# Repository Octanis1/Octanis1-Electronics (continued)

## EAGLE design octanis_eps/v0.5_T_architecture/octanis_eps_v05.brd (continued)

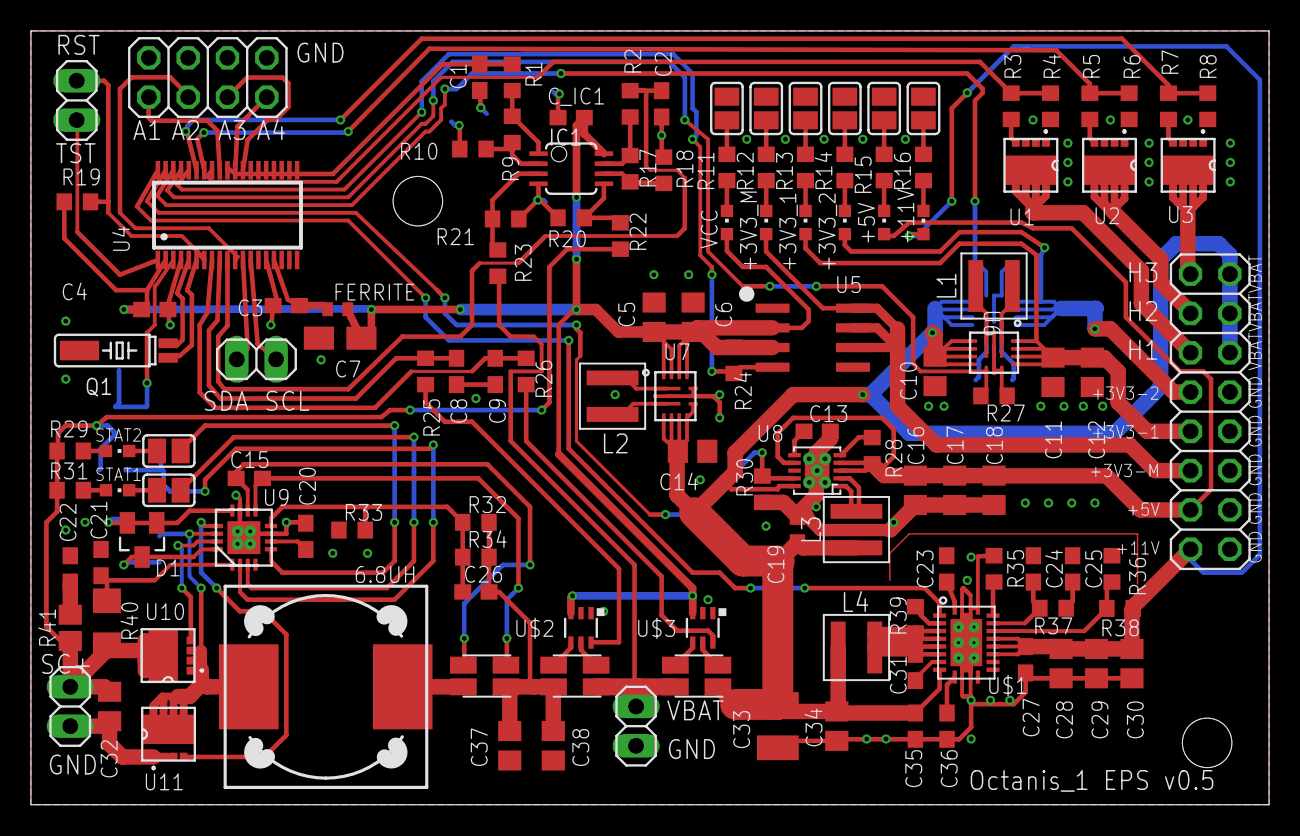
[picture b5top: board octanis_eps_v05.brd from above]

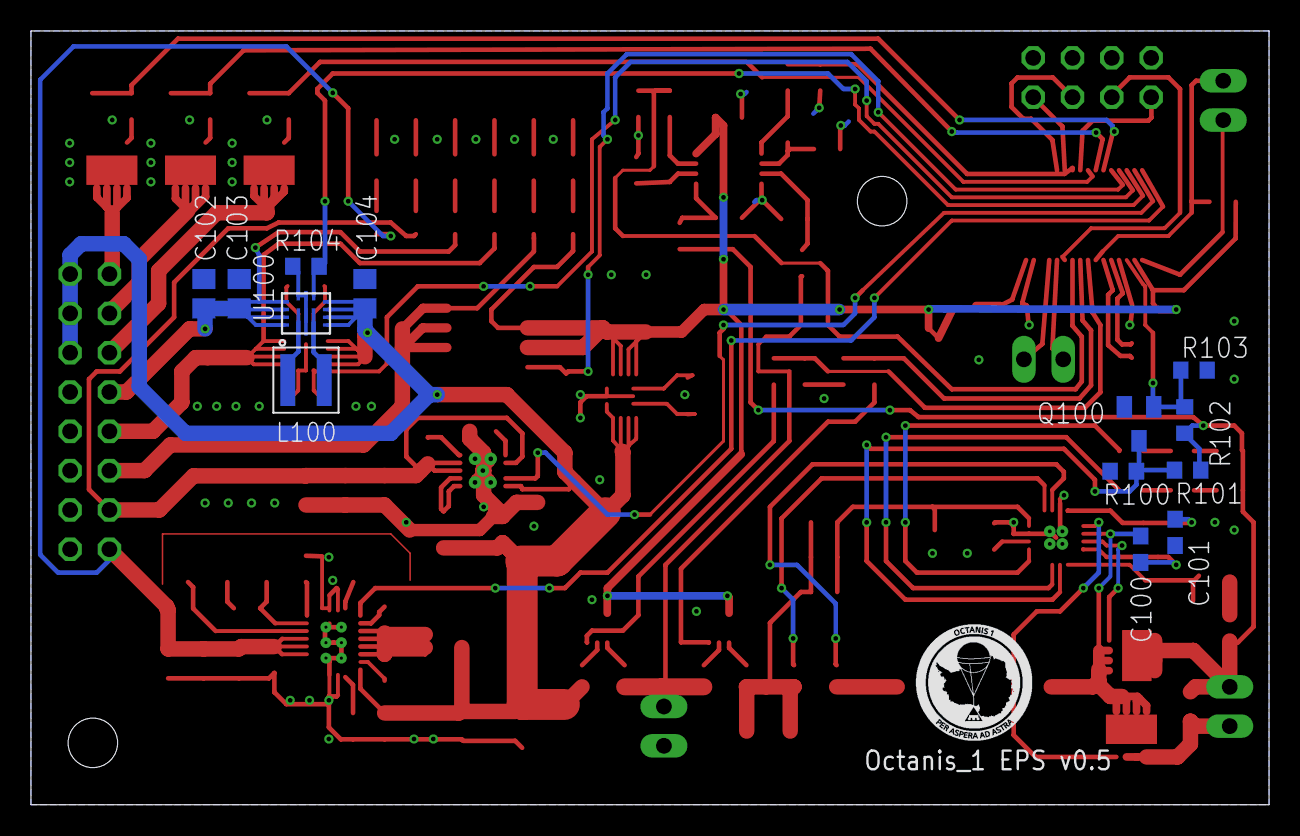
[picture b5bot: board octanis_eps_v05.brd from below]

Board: 2 copper layers, 80.0 x 50.0 mm, 141 parts (13 on the bottom side), 102 nets.

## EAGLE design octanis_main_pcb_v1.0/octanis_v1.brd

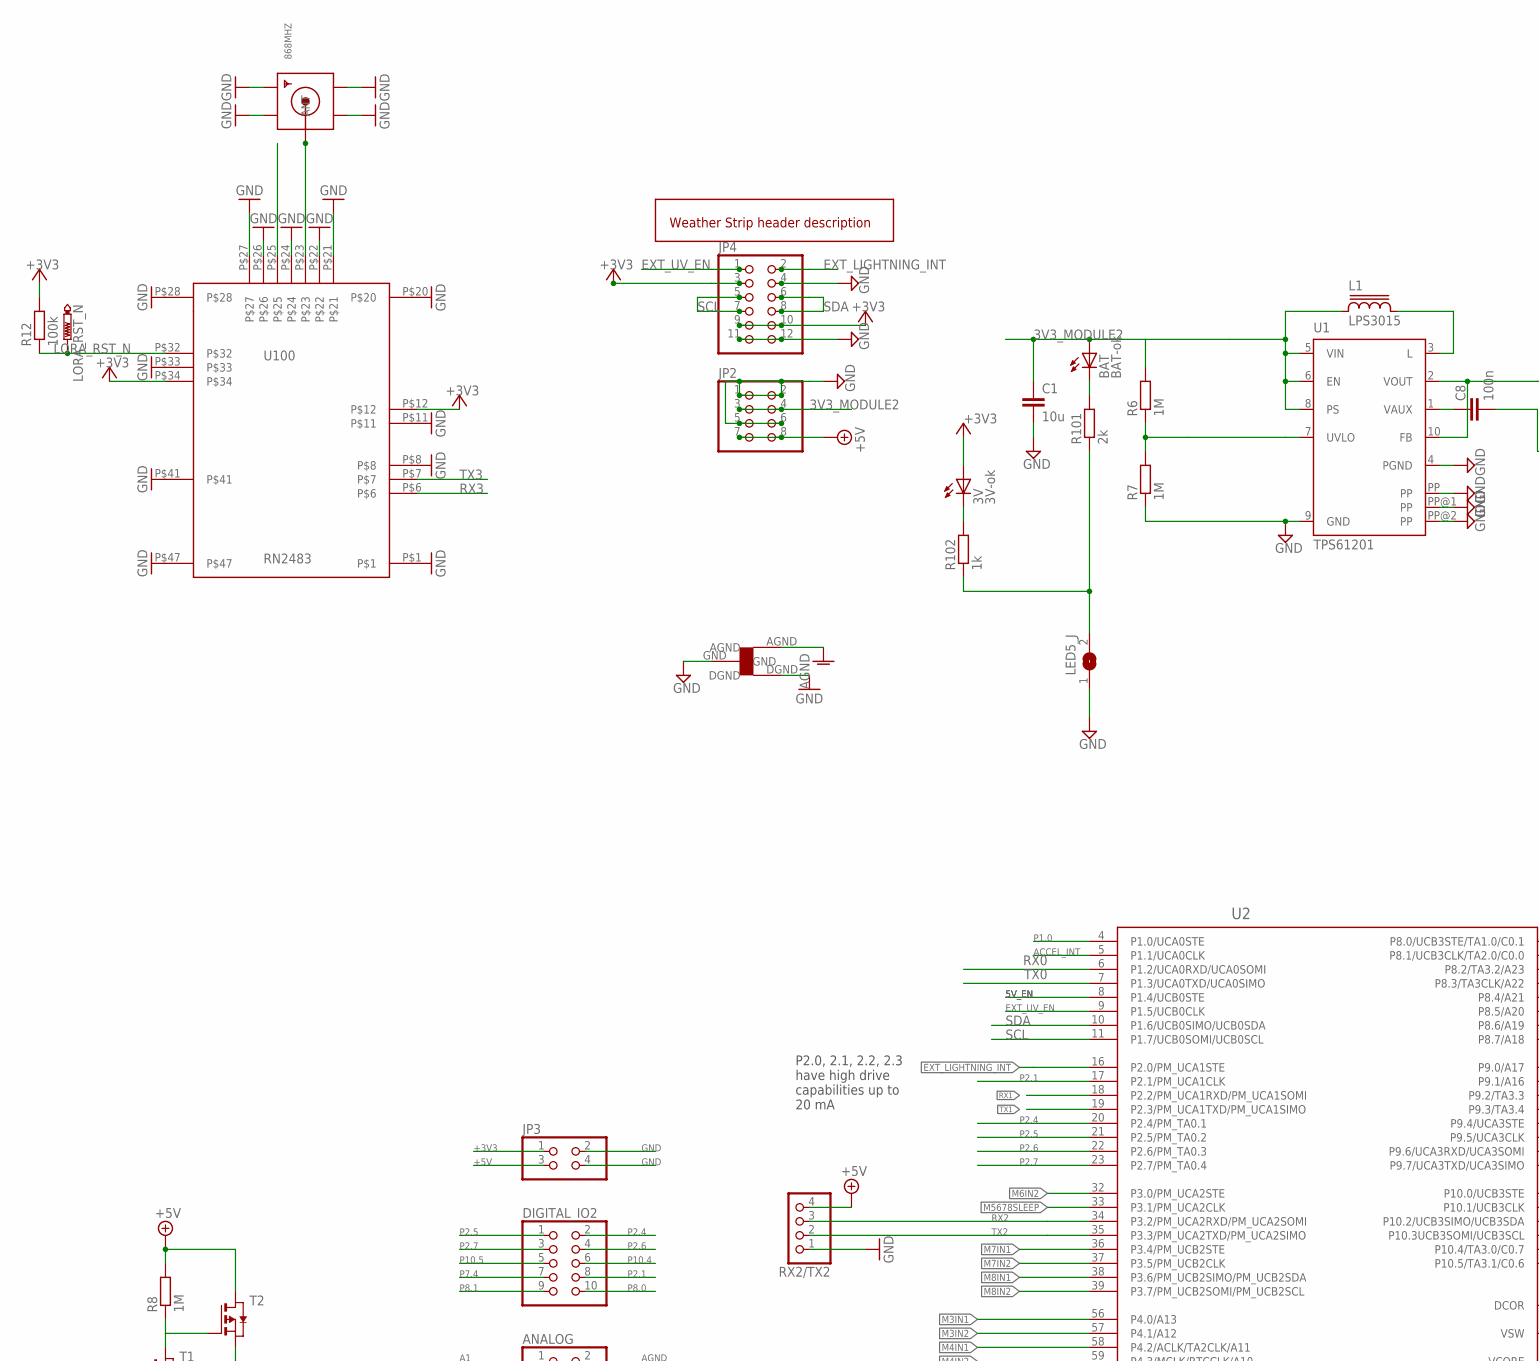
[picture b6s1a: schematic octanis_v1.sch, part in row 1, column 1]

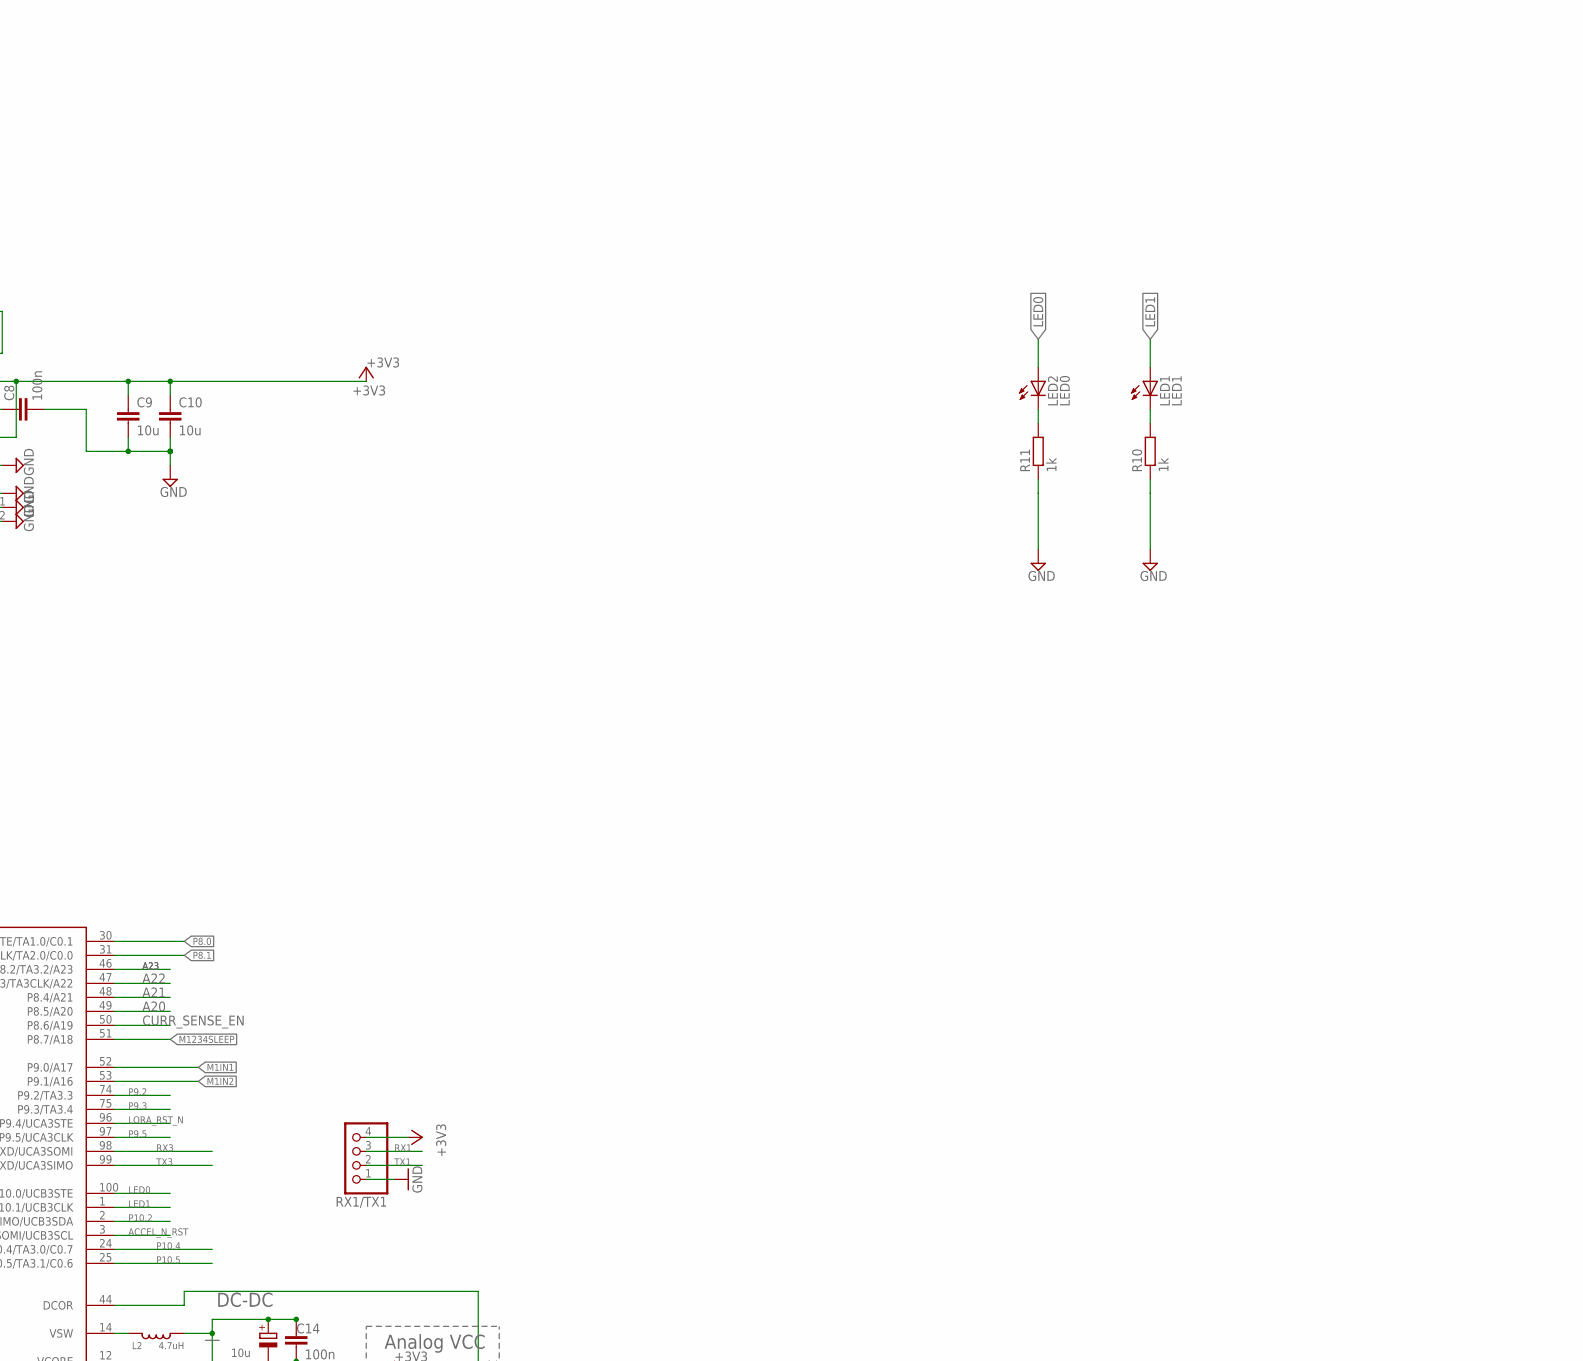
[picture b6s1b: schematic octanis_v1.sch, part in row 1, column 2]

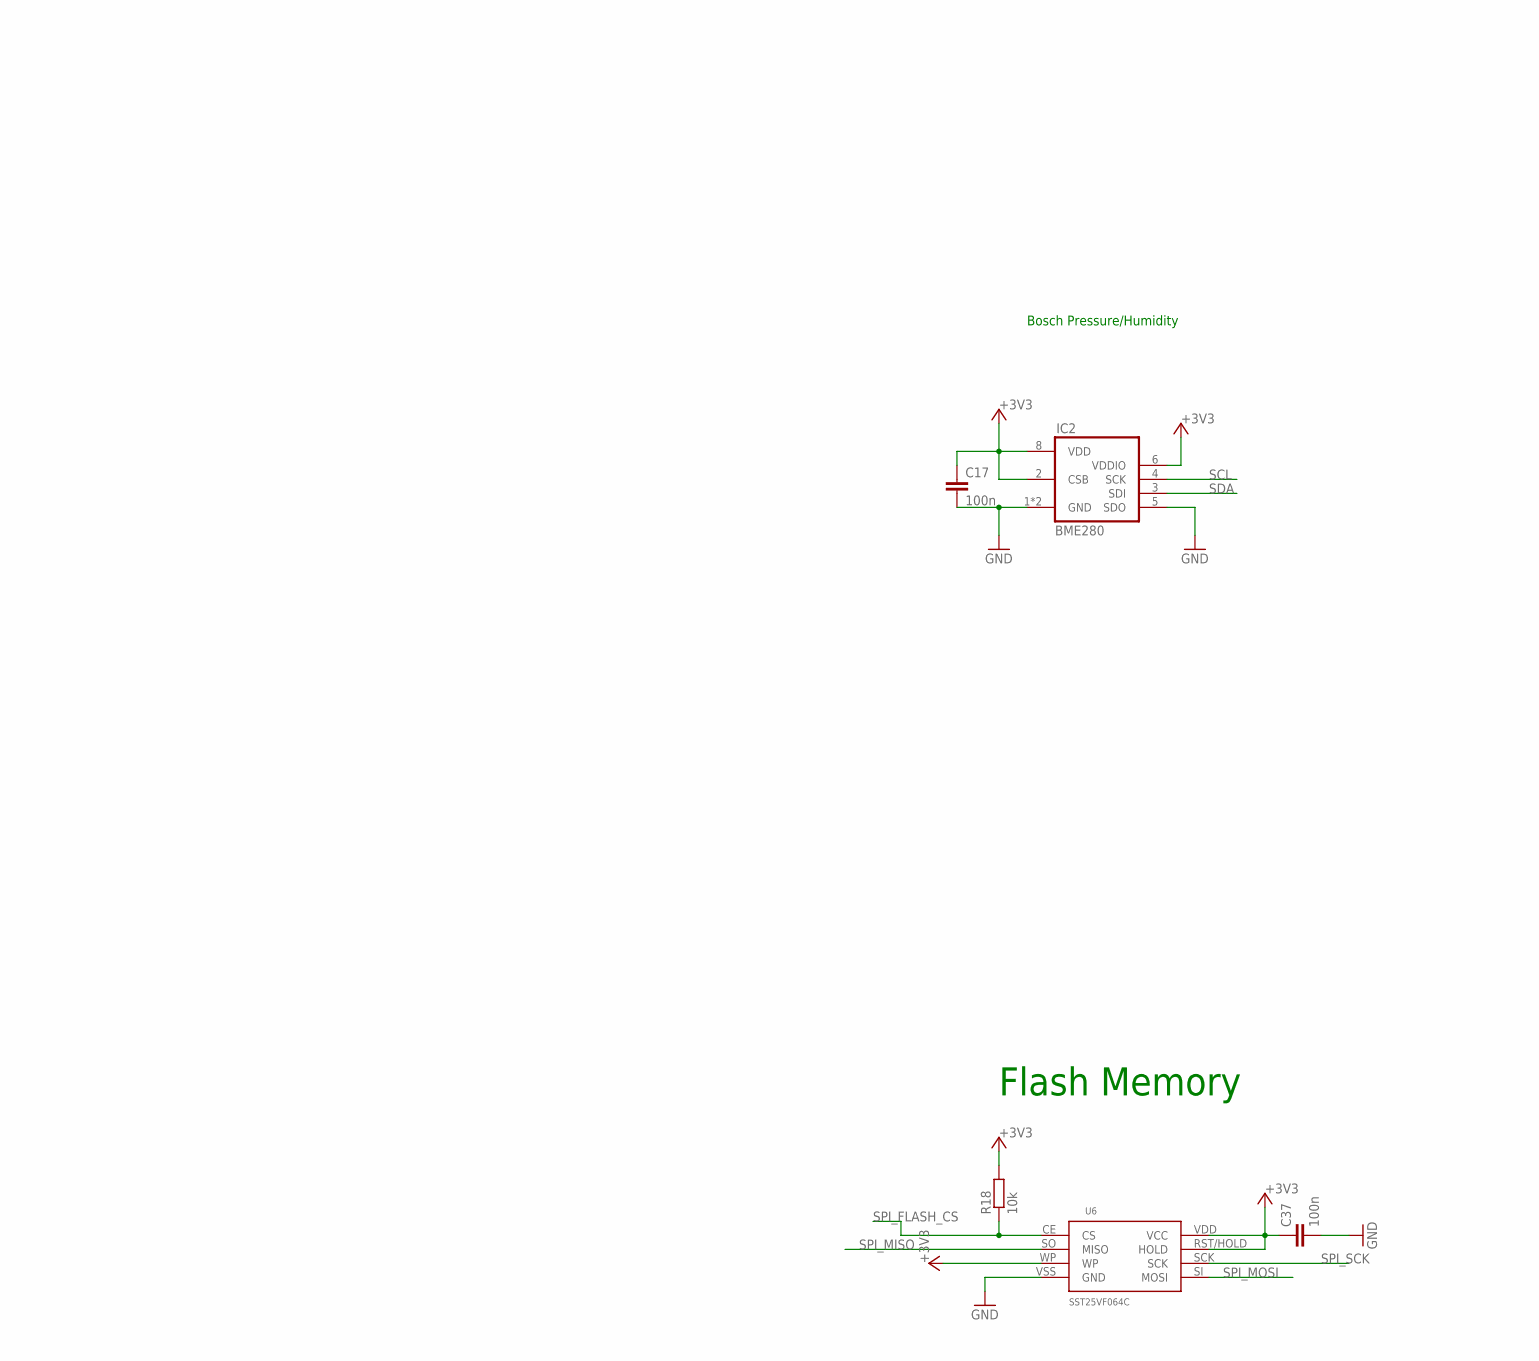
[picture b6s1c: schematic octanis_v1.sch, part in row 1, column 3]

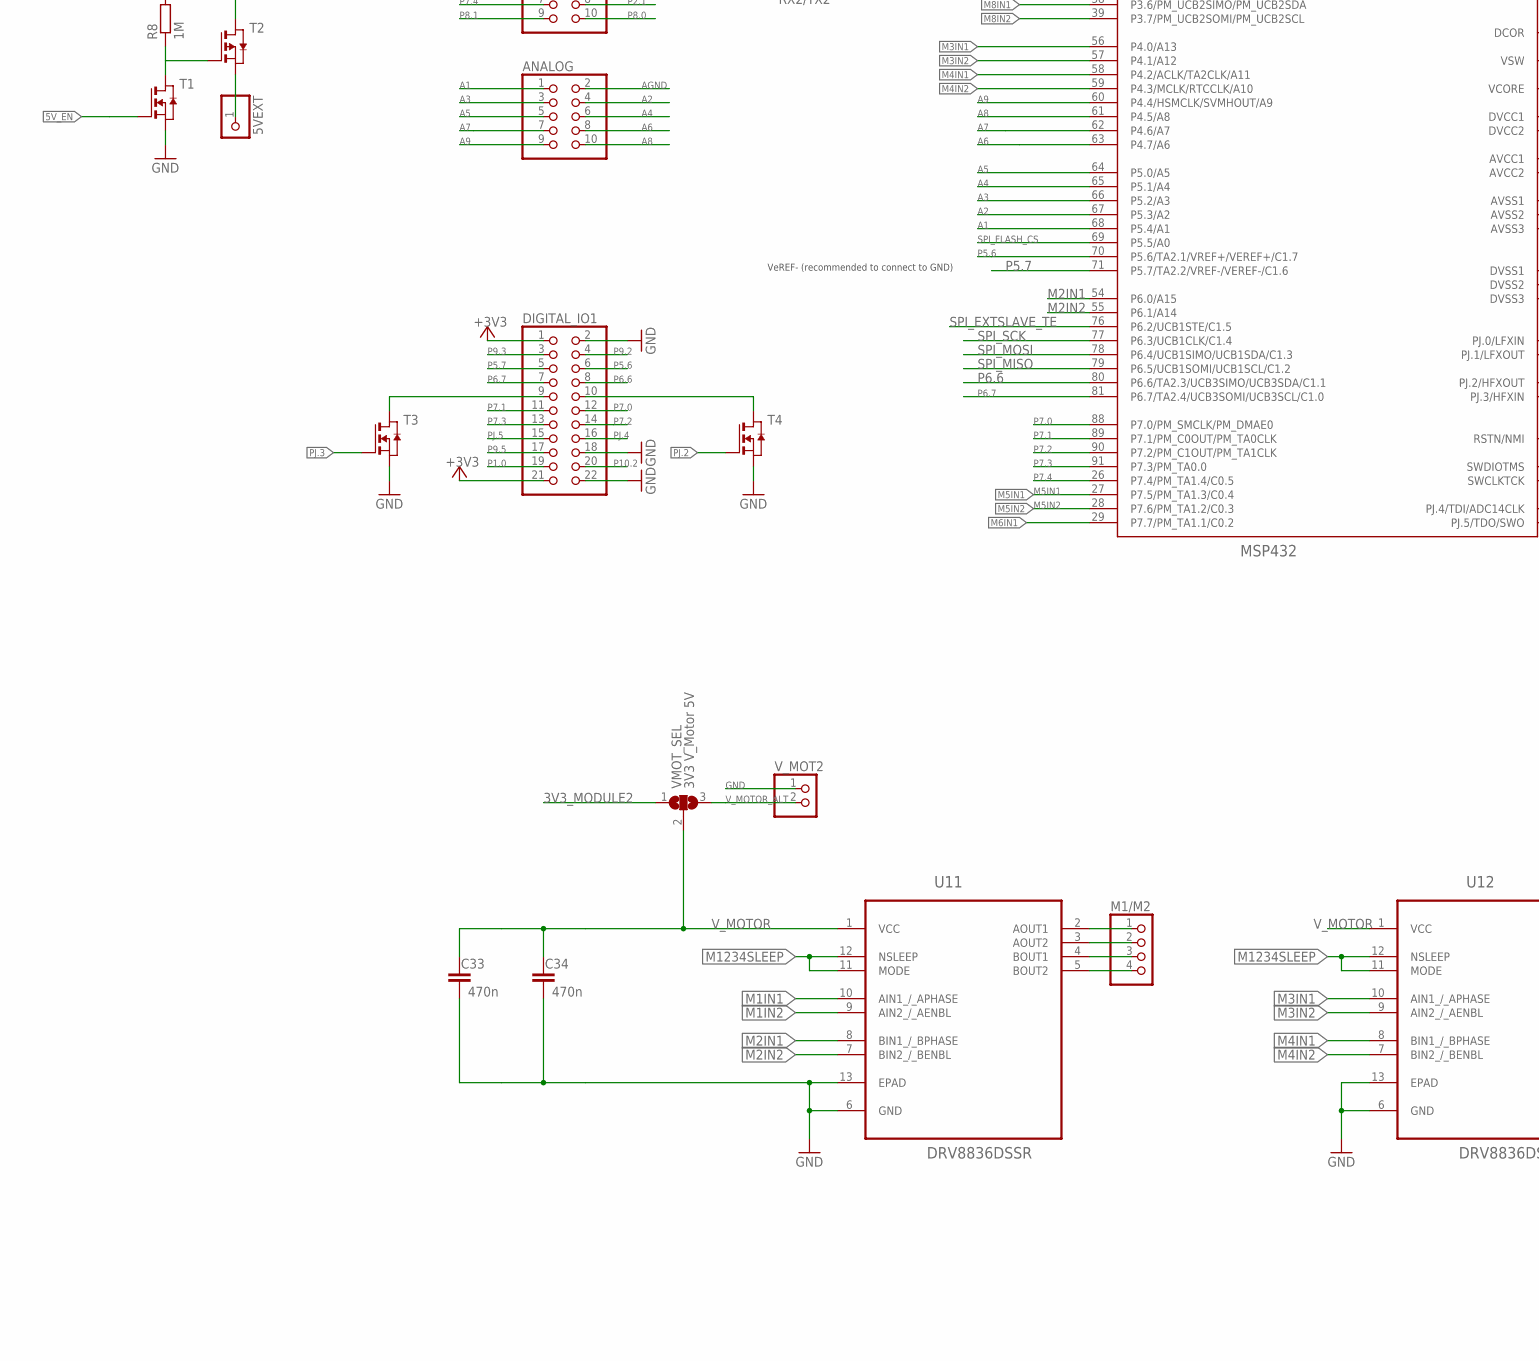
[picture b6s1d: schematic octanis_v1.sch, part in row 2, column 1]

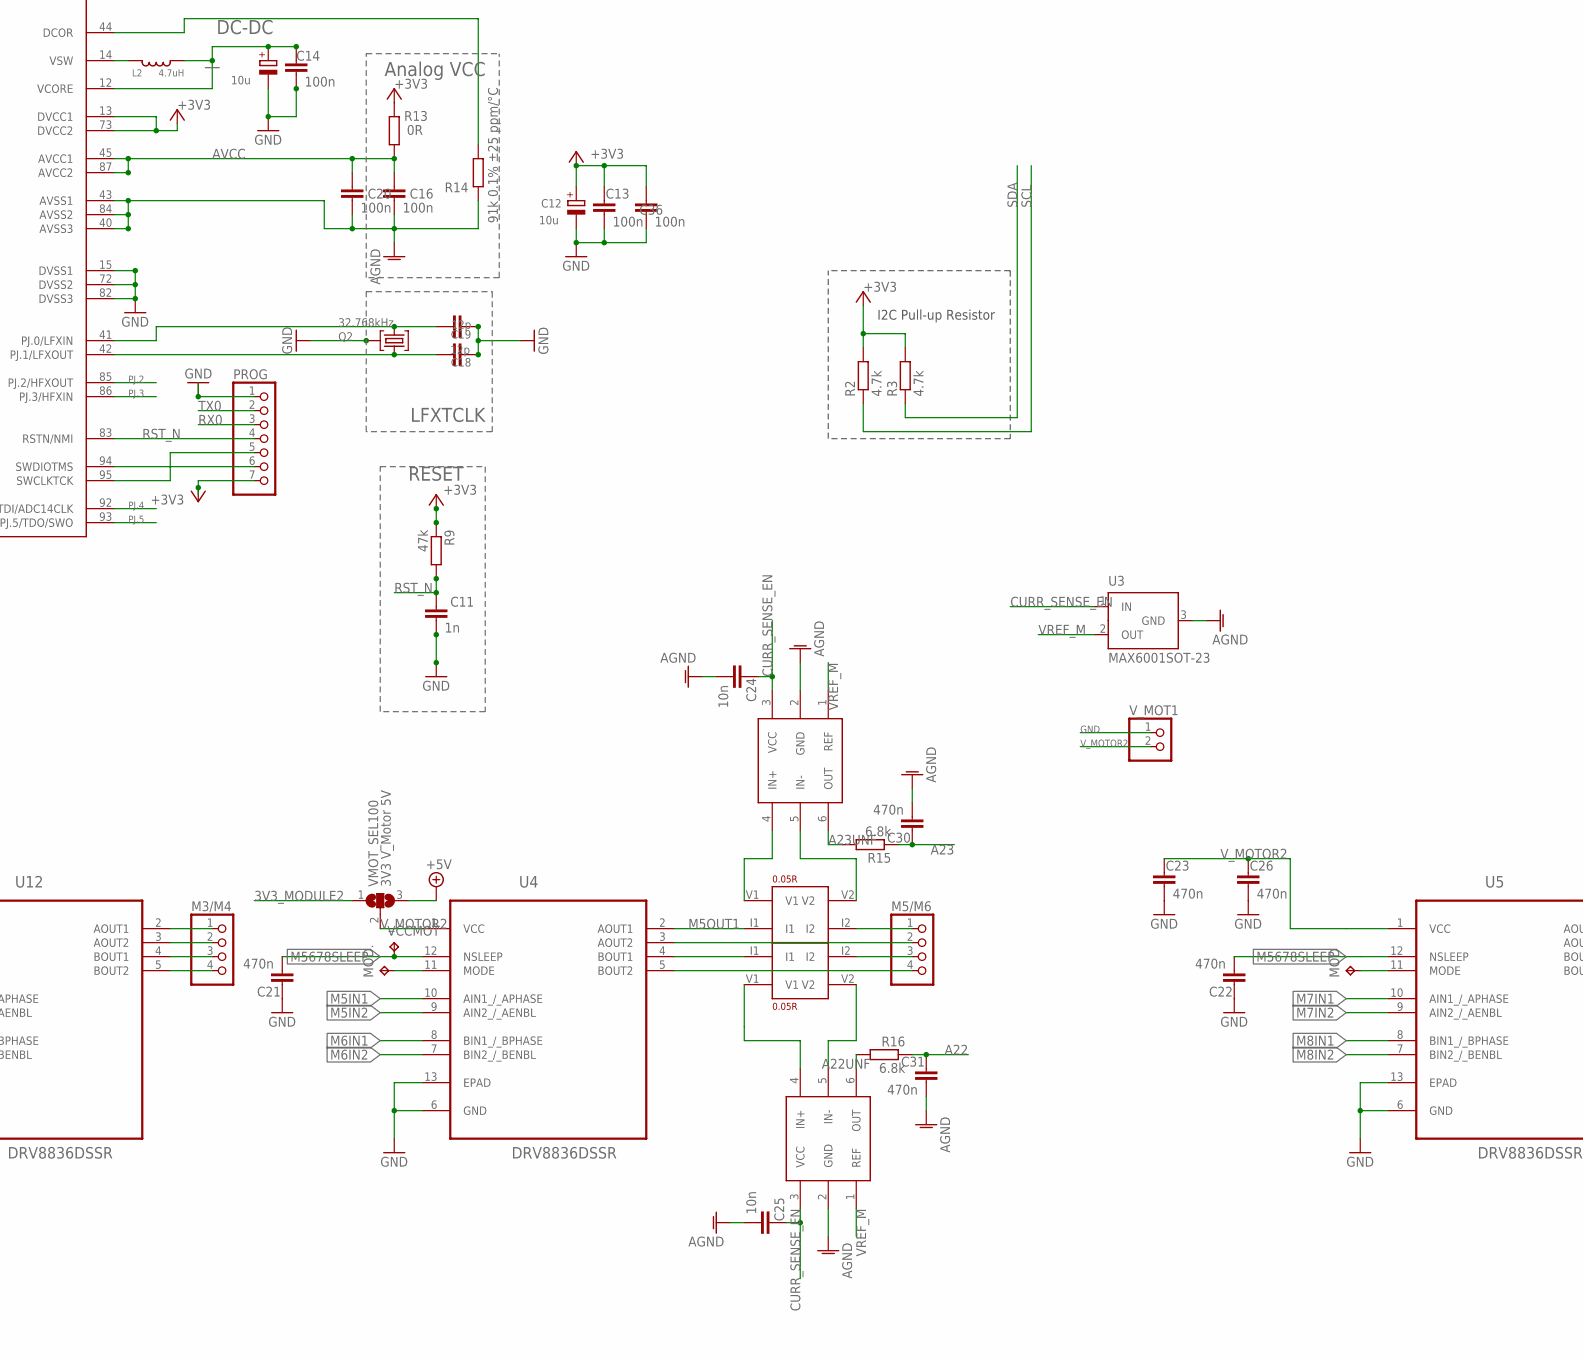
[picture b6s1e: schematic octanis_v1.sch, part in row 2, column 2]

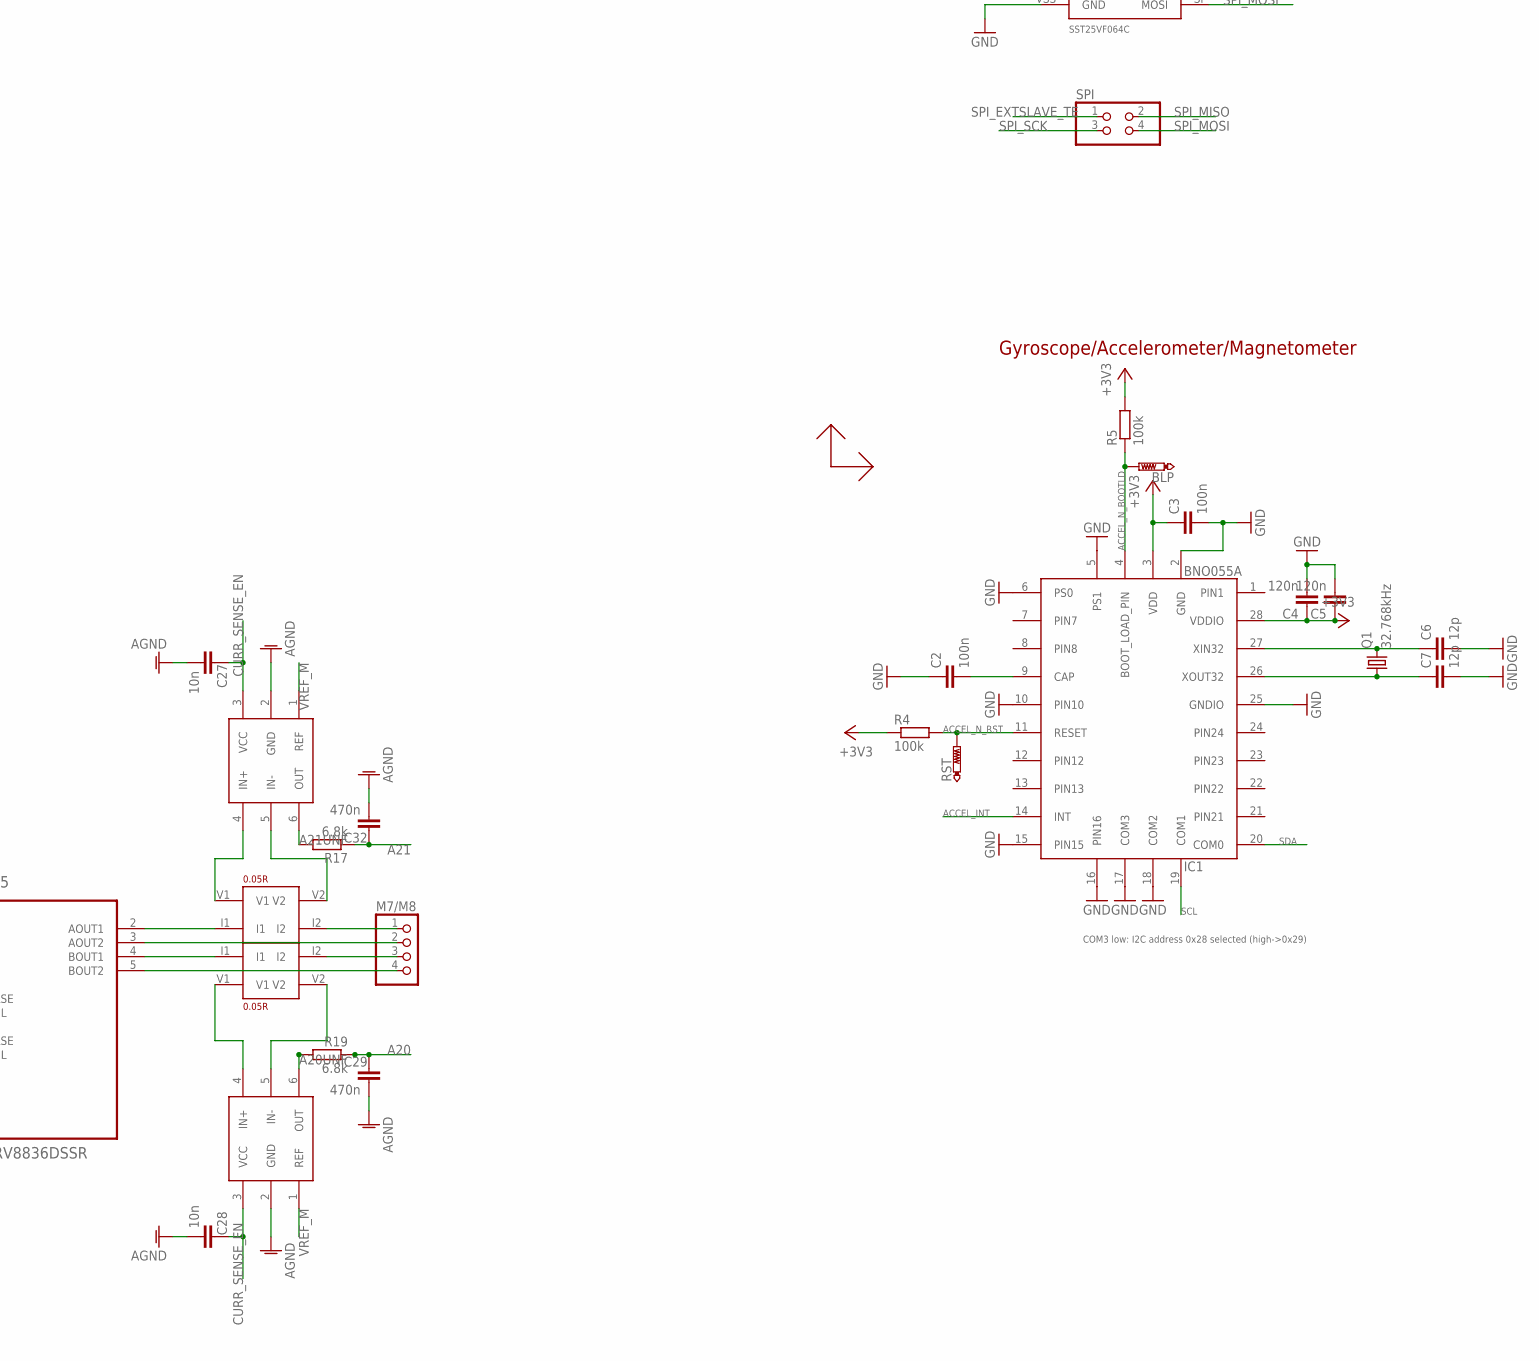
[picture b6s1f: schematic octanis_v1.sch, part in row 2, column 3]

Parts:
3V: 3V-ok; CHIPLED_0603
5VEXT: PINHD-1X1; 1X01
868MHZ: SMACONNECTOR_EDGE; SMA_EDGELAUNCH
ANALOG: PINHD-2X5; 2X05
BAT: BAT-ok; CHIPLED_0603
BLP: PTR1B1,27; B1,27
C1, C9, C10: 10u; C0805K
C2, C3, C8, C13, C14, C17, C36, C37: 100n; C0603
C4, C5: 120n; C0603
C6, C7: 12p; C0603
C11: 1n; C0603
C12, C15: 10u; A/3216-18R
C16, C20: 100n; C0402
C18, C19: 12p; C0402
C21, C22, C23, C26, C29, C30, C31, C32, C33, C34: 470n; C0603
C24, C25, C27, C28: 10n; C0603
DIGITAL_IO1: PINHD-2X11; 2X11
DIGITAL_IO2: PINHD-2X5; 2X05
IC1: BNO055A; BNO055
IC2: BME280
JP2: PINHD-2X04_2.54; 2X04
JP3: PINHD-2X2; 2X02
JP4: PINHD-2X06_2.54-SMD; 2X06SMD
L1: LPS3015
L2: 4.7uH; 0806
LED1: LED1; CHIPLED_0603
LED2: LED0; CHIPLED_0603
LED5_J: SJ
LORA_RST_N: PTR1TP15R; TP15R
M1/M2, M3/M4, M5/M6, M7/M8: PINHD-1X04_2.54-S; 1X04-S
MOD, MOD.: TPTP06R; TP06R
PROG: PINHD-1X72MM_SMD; 1X7SMD
Q1: 32.768kHz; FC-12M
Q2: 32.768kHz; MS3V-T1R
R2, R3: 4.7k; R0603
R4, R5, R12: 100k; R0603
R6, R7, R8: 1M; R0603
R9: 47k; R0603
R10, R11, R102: 1k; R0603
R13: 0R; R0402
R14: 91k 0.1% ±25 ppm/°C; R0402
R15, R16, R17, R19: 6.8k; R0603
R18: 10k; R0603
R101: 2k; R0603
RS1, RS2, RS3, RS4: 0.05R; 4PADS_RESISTOR
RST: PTR1B1,27; B1,27
RX1/TX1, RX2/TX2: PINHD-1X04_2.54-S; 1X04-S
SPI: PINHD-2X2; 2X02
T1, T3, T4: NMOSSOT23; SOT-23
T2: PMOSSOT23; SOT-23
U1: TPS61201; S-PDSO-N10
U2: MSP432; PZ100
U3: MAX6001SOT-23; MAX6001
U4, U5, U11, U12: DRV8836DSSR; SON50P200X300X80-13N
U6: SST25VF064C; SOIC_8-LEAD
U7, U8, U9, U10: INA210; SC70-6
U100: RN2483
U$1: WEATHER_STRIP_DOCU
U$2: STARGND; STAR
U$3: BNO055_COORDINATES
VCCMOT: TPTP06R; TP06R
VMOT_SEL, VMOT_SEL100: 3V3 V_Motor 5V; SJ_2
V_MOT1, V_MOT2: PINHD-1X02_2.54-S; 1X02-S

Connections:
3V3_MODULE2: BAT.A, C1.1, JP2.3, JP2.4, L1.1, R6.2, U1.5 (VIN), U1.6 (EN), U1.8 (PS), VMOT_SEL.1, VMOT_SEL100.1
5V_EN: T1.3 (G), U2.8 (P1.4/UCB0STE)
+3V3: 3V.A, C3.1, C4.1, C5.1, C9.1, C10.1, C12.+, C13.2, C17.1, C36.2, C37.1, DIGITAL_IO1.1, DIGITAL_IO1.21, IC1.3 (VDD), IC1.28 (VDDIO), IC2.2 (CSB), IC2.6 (VDDIO), IC2.8 (VDD), JP3.1, JP4.3, JP4.9, JP4.10, PROG.7, R2.2, R3.2, R4.1, R5.2, R9.1, R12.2, R13.2, R18.2, RX1/TX1.4, U1.2 (VOUT), U1.10 (FB), U2.13 (DVCC1), U2.73 (DVCC2), U6.RST/HOLD (HOLD), U6.VDD (VCC), U6.WP, U100.P$12, U100.P$34
+5V: JP2.7, JP2.8, JP3.3, R8.2, RX2/TX2.4, T2.1 (D), VMOT_SEL100.3
A1: ANALOG.1, U2.68 (P5.4/A1)
A2: ANALOG.4, U2.67 (P5.3/A2)
A3: ANALOG.3, U2.66 (P5.2/A3)
A4: ANALOG.6, U2.65 (P5.1/A4)
A5: ANALOG.5, U2.64 (P5.0/A5)
A6: ANALOG.8, U2.63 (P4.7/A6)
A7: ANALOG.7, U2.62 (P4.6/A7)
A8: ANALOG.10, U2.61 (P4.5/A8)
A9: ANALOG.9, U2.60 (P4.4/HSMCLK/SVMHOUT/A9)
A20: C29.2, R19.1, U2.49 (P8.5/A20)
A20UNF: R19.2, U10.6 (OUT)
A21: C32.2, R17.1, U2.48 (P8.4/A21)
A21UNF: R17.2, U9.6 (OUT)
A22: C31.2, R16.1, U2.47 (P8.3/TA3CLK/A22)
A22UNF: R16.2, U8.6 (OUT)
A23: C30.2, R15.1, U2.46 (P8.2/TA3.2/A23)
A23UNF: R15.2, U7.6 (OUT)
ACCEL_INT: IC1.14 (INT), U2.5 (P1.1/UCA0CLK)
ACCEL_N_BOOTLD: BLP.TP, IC1.4 (BOOT_LOAD_PIN), R5.1
ACCEL_N_RST: IC1.11 (RESET), R4.2, RST.TP, U2.3 (P10.3UCB3SOMI/UCB3SCL)
AGND: ANALOG.2, C16.2, C20.2, C24.1, C25.1, C27.1, C28.1, C29.1, C30.1, C31.1, C32.1, R14.2, U2.40 (AVSS3), U2.43 (AVSS1), U2.84 (AVSS2), U3.3 (GND), U7.2 (GND), U8.2 (GND), U9.2 (GND), U10.2 (GND), U$2.AGND
ANT433: U100.P$25
ANT868: 868MHZ.P (ANT), U100.P$23
AVCC: C16.1, C20.1, R13.1, U2.45 (AVCC1), U2.87 (AVCC2)
CURR_SENSE_EN: C24.2, C25.2, C27.2, C28.2, U2.50 (P8.6/A19), U3.1 (IN), U7.3 (VCC), U8.3 (VCC), U9.3 (VCC), U10.3 (VCC)
EXT_LIGHTNING_INT: JP4.2, U2.16 (P2.0/PM_UCA1STE)
EXT_UV_EN: JP4.1, U2.9 (P1.5/UCB0CLK)
GND: 868MHZ.GND@1 (GND4), 868MHZ.GND@2 (GND3), 868MHZ.GND@3 (GND2), 868MHZ.GND@4 (GND1), C1.2, C2.1, C3.2, C4.2, C5.2, C6.2, C7.2, C8.2, C9.2, C10.2, C11.1, C12.-, C13.1, C14.1, C15.-, C17.2, C18.1, C19.1, C21.2, C22.2, C23.1, C26.1, C33.1, C34.1, C36.1, C37.2, DIGITAL_IO1.2, DIGITAL_IO1.18, DIGITAL_IO1.22, IC1.2 (GND), IC1.5 (PS1), IC1.6 (PS0), IC1.10 (PIN10), IC1.15 (PIN15), IC1.16 (PIN16), IC1.17 (COM3), IC1.18 (COM2), IC1.25 (GNDIO), IC2.1 (GND), IC2.5 (SDO), IC2.7 (GND), JP2.1, JP2.2, JP2.5, JP2.6, JP3.2, JP3.4, JP4.4, JP4.11, JP4.12, LED5_J.1, PROG.1, Q2.P3 (GND), R7.1, R10.1, R11.1, RX1/TX1.1, RX2/TX2.1, T1.2 (S), T3.2 (S), T4.2 (S), U1.4 (PGND), U1.9 (GND), U1.PP, U1.PP@1 (PP), U1.PP@2 (PP), U2.15 (DVSS1), U2.72 (DVSS2), U2.82 (DVSS3), U4.6 (GND), U4.13 (EPAD), U5.6 (GND), U5.13 (EPAD), U6.VSS (GND), U11.6 (GND), U11.13 (EPAD), U12.6 (GND), U12.13 (EPAD), U100.P$1, U100.P$8, U100.P$11, U100.P$20, U100.P$21, U100.P$22, U100.P$24, U100.P$26, U100.P$27, U100.P$28, U100.P$33, U100.P$41, U100.P$47, U$2.DGND, U$2.GND, V_MOT1.1, V_MOT2.1
L: L1.2, U1.3 (L)
LED0: LED2.A, U2.100 (P10.0/UCB3STE)
LED1: LED1.A, U2.1 (P10.1/UCB3CLK)
LORA_RST_N: LORA_RST_N.TP, R12.1, U2.96 (P9.4/UCA3STE), U100.P$32
M1IN1: U2.52 (P9.0/A17), U11.10 (AIN1_/_APHASE)
M1IN2: U2.53 (P9.1/A16), U11.9 (AIN2_/_AENBL)
M2IN1: U2.54 (P6.0/A15), U11.8 (BIN1_/_BPHASE)
M2IN2: U2.55 (P6.1/A14), U11.7 (BIN2_/_BENBL)
M3IN1: U2.56 (P4.0/A13), U12.10 (AIN1_/_APHASE)
M3IN2: U2.57 (P4.1/A12), U12.9 (AIN2_/_AENBL)
M4IN1: U2.58 (P4.2/ACLK/TA2CLK/A11), U12.8 (BIN1_/_BPHASE)
M4IN2: U2.59 (P4.3/MCLK/RTCCLK/A10), U12.7 (BIN2_/_BENBL)
M5IN1: U2.27 (P7.5/PM_TA1.3/C0.4), U4.10 (AIN1_/_APHASE)
M5IN2: U2.28 (P7.6/PM_TA1.2/C0.3), U4.9 (AIN2_/_AENBL)
M5OUT1: RS1.I1, U4.2 (AOUT1)
M6IN1: U2.29 (P7.7/PM_TA1.1/C0.2), U4.8 (BIN1_/_BPHASE)
M6IN2: U2.32 (P3.0/PM_UCA2STE), U4.7 (BIN2_/_BENBL)
M7IN1: U2.36 (P3.4/PM_UCB2STE), U5.10 (AIN1_/_APHASE)
M7IN2: U2.37 (P3.5/PM_UCB2CLK), U5.9 (AIN2_/_AENBL)
M8IN1: U2.38 (P3.6/PM_UCB2SIMO/PM_UCB2SDA), U5.8 (BIN1_/_BPHASE)
M8IN2: U2.39 (P3.7/PM_UCB2SOMI/PM_UCB2SCL), U5.7 (BIN2_/_BENBL)
M1234SLEEP: U2.51 (P8.7/A18), U11.11 (MODE), U11.12 (NSLEEP), U12.11 (MODE), U12.12 (NSLEEP)
M5678SLEEP: C21.1, C22.1, U2.33 (P3.1/PM_UCA2CLK), U4.12 (NSLEEP), U5.12 (NSLEEP), VCCMOT.TP
unnamed: C14.2, C15.+, L2.1, U2.12 (VCORE)
unnamed: C8.1, U1.1 (VAUX)
unnamed: 3V.C, R102.2
unnamed: LED2.C, R11.2
unnamed: LED1.C, R10.2
unnamed: C18.2, Q2.P2 (2), U2.41 (PJ.0/LFXIN)
unnamed: C19.2, Q2.P1 (1), U2.42 (PJ.1/LFXOUT)
unnamed: M3/M4.1, U12.2 (AOUT1)
unnamed: R8.1, T1.1 (D), T2.3 (G)
unnamed: RS1.V2, U7.5 (IN-)
unnamed: RS1.V1, U7.4 (IN+)
unnamed: C2.2, IC1.9 (CAP)
unnamed: C6.1, IC1.27 (XIN32), Q1.2
unnamed: MOD.TP, U5.11 (MODE)
unnamed: M5/M6.1, RS1.I2
unnamed: MOD..TP, U4.11 (MODE)
unnamed: RS2.V1, U8.4 (IN+)
unnamed: RS2.V2, U8.5 (IN-)
unnamed: RS2.I1, U4.4 (BOUT1)
unnamed: LED5_J.2, R101.1, R102.1
unnamed: M5/M6.3, RS2.I2
unnamed: RS3.V2, U9.5 (IN-)
unnamed: RS3.V1, U9.4 (IN+)
unnamed: RS4.V2, U10.5 (IN-)
unnamed: RS4.V1, U10.4 (IN+)
unnamed: M7/M8.1, RS3.I2
unnamed: R14.1, U2.44 (DCOR)
unnamed: L2.2, U2.14 (VSW)
unnamed: RS4.I1, U5.4 (BOUT1)
unnamed: RS3.I1, U5.2 (AOUT1)
unnamed: M7/M8.3, RS4.I2
unnamed: M5/M6.2, U4.3 (AOUT2)
unnamed: M3/M4.2, U12.3 (AOUT2)
unnamed: M3/M4.3, U12.4 (BOUT1)
unnamed: M3/M4.4, U12.5 (BOUT2)
unnamed: R6.1, R7.2, U1.7 (UVLO)
unnamed: M5/M6.4, U4.5 (BOUT2)
unnamed: BAT.C, R101.2
unnamed: M7/M8.4, U5.5 (BOUT2)
unnamed: DIGITAL_IO1.9, T3.1 (D)
unnamed: 5VEXT.1, T2.2 (S)
unnamed: M1/M2.1, U11.2 (AOUT1)
unnamed: M1/M2.2, U11.3 (AOUT2)
unnamed: M1/M2.3, U11.4 (BOUT1)
unnamed: M1/M2.4, U11.5 (BOUT2)
unnamed: M7/M8.2, U5.3 (AOUT2)
unnamed: DIGITAL_IO1.10, T4.1 (D)
unnamed: C7.1, IC1.26 (XOUT32), Q1.1
unnamed: PROG.6, U2.94 (SWDIOTMS)
unnamed: PROG.5, U2.95 (SWCLKTCK)
P1.0: DIGITAL_IO1.19, U2.4 (P1.0/UCA0STE)
P2.1: DIGITAL_IO2.8, U2.17 (P2.1/PM_UCA1CLK)
P2.4: DIGITAL_IO2.2, U2.20 (P2.4/PM_TA0.1)
P2.5: DIGITAL_IO2.1, U2.21 (P2.5/PM_TA0.2)
P2.6: DIGITAL_IO2.4, U2.22 (P2.6/PM_TA0.3)
P2.7: DIGITAL_IO2.3, U2.23 (P2.7/PM_TA0.4)
P5.6: DIGITAL_IO1.6, U2.70 (P5.6/TA2.1/VREF+/VEREF+/C1.7)
P5.7: DIGITAL_IO1.5, U2.71 (P5.7/TA2.2/VREF-/VEREF-/C1.6)
P6.6: DIGITAL_IO1.8, U2.80 (P6.6/TA2.3/UCB3SIMO/UCB3SDA/C1.1)
P6.7: DIGITAL_IO1.7, U2.81 (P6.7/TA2.4/UCB3SOMI/UCB3SCL/C1.0)
P7.0: DIGITAL_IO1.12, U2.88 (P7.0/PM_SMCLK/PM_DMAE0)
P7.1: DIGITAL_IO1.11, U2.89 (P7.1/PM_C0OUT/PM_TA0CLK)
P7.2: DIGITAL_IO1.14, U2.90 (P7.2/PM_C1OUT/PM_TA1CLK)
P7.3: DIGITAL_IO1.13, U2.91 (P7.3/PM_TA0.0)
P7.4: DIGITAL_IO2.7, U2.26 (P7.4/PM_TA1.4/C0.5)
P8.0: DIGITAL_IO2.10, U2.30 (P8.0/UCB3STE/TA1.0/C0.1)
P8.1: DIGITAL_IO2.9, U2.31 (P8.1/UCB3CLK/TA2.0/C0.0)
P9.2: DIGITAL_IO1.4, U2.74 (P9.2/TA3.3)
P9.3: DIGITAL_IO1.3, U2.75 (P9.3/TA3.4)
P9.5: DIGITAL_IO1.17, U2.97 (P9.5/UCA3CLK)
P10.2: DIGITAL_IO1.20, U2.2 (P10.2/UCB3SIMO/UCB3SDA)
P10.4: DIGITAL_IO2.6, U2.24 (P10.4/TA3.0/C0.7)
P10.5: DIGITAL_IO2.5, U2.25 (P10.5/TA3.1/C0.6)
PJ.2: T4.3 (G), U2.85 (PJ.2/HFXOUT)
PJ.3: T3.3 (G), U2.86 (PJ.3/HFXIN)
PJ.4: DIGITAL_IO1.16, U2.92 (PJ.4/TDI/ADC14CLK)
PJ.5: DIGITAL_IO1.15, U2.93 (PJ.5/TDO/SWO)
RST_N: C11.2, PROG.4, R9.2, U2.83 (RSTN/NMI)
RX0: PROG.3, U2.6 (P1.2/UCA0RXD/UCA0SOMI)
RX1: RX1/TX1.3, U2.18 (P2.2/PM_UCA1RXD/PM_UCA1SOMI)
RX2: RX2/TX2.3, U2.34 (P3.2/PM_UCA2RXD/PM_UCA2SOMI)
RX3: U2.98 (P9.6/UCA3RXD/UCA3SOMI), U100.P$6
SCL: IC1.19 (COM1), IC2.4 (SCK), JP4.5, JP4.7, R2.1, U2.11 (P1.7/UCB0SOMI/UCB0SCL)
SDA: IC1.20 (COM0), IC2.3 (SDI), JP4.6, JP4.8, R3.1, U2.10 (P1.6/UCB0SIMO/UCB0SDA)
SPI_EXTSLAVE_TE: SPI.1, U2.76 (P6.2/UCB1STE/C1.5)
SPI_FLASH_CS: R18.1, U2.69 (P5.5/A0), U6.CE (CS)
SPI_MISO: SPI.2, U2.79 (P6.5/UCB1SOMI/UCB1SCL/C1.2), U6.SO (MISO)
SPI_MOSI: SPI.4, U2.78 (P6.4/UCB1SIMO/UCB1SDA/C1.3), U6.SI (MOSI)
SPI_SCK: SPI.3, U2.77 (P6.3/UCB1CLK/C1.4), U6.SCK
TX0: PROG.2, U2.7 (P1.3/UCA0TXD/UCA0SIMO)
TX1: RX1/TX1.2, U2.19 (P2.3/PM_UCA1TXD/PM_UCA1SIMO)
TX2: RX2/TX2.2, U2.35 (P3.3/PM_UCA2TXD/PM_UCA2SIMO)
TX3: U2.99 (P9.7/UCA3TXD/UCA3SIMO), U100.P$7
VREF_M: U3.2 (OUT), U7.1 (REF), U8.1 (REF), U9.1 (REF), U10.1 (REF)
V_MOTOR: C33.2, C34.2, U11.1 (VCC), U12.1 (VCC), VMOT_SEL.2
V_MOTOR2: C23.2, C26.2, U4.1 (VCC), U5.1 (VCC), VMOT_SEL100.2, V_MOT1.2
V_MOTOR_ALT: VMOT_SEL.3, V_MOT2.2

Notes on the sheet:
LFXTCLK
Analog VCC
I2C Pull-up Resistor
Flash Memory
Gyroscope/Accelerometer/Magnetometer
Bosch Pressure/Humidity
DC-DC
COM3 low: I2C address 0x28 selected (high->0x29)
VeREF- (recommended to connect to GND)
RESET
P2.0, 2.1, 2.2, 2.3 have high drive capabilities up to 20 mA
